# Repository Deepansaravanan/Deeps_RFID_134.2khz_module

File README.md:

Feedback Request
Hello! I have posted this project on GitHub but I'm unsure whether it is correct or if there are issues. If anyone with knowledge in this area can help me review or fix any problems, I would greatly appreciate your feedback and suggestions.

Please let me know if you spot mistakes, bugs, or unnecessary code.

Share advice on how I can improve the project or make it more robust.

If you have time, feel free to open an issue or pull request with corrections and explanations.

Thanks in advance for any help or feedback you can provide!

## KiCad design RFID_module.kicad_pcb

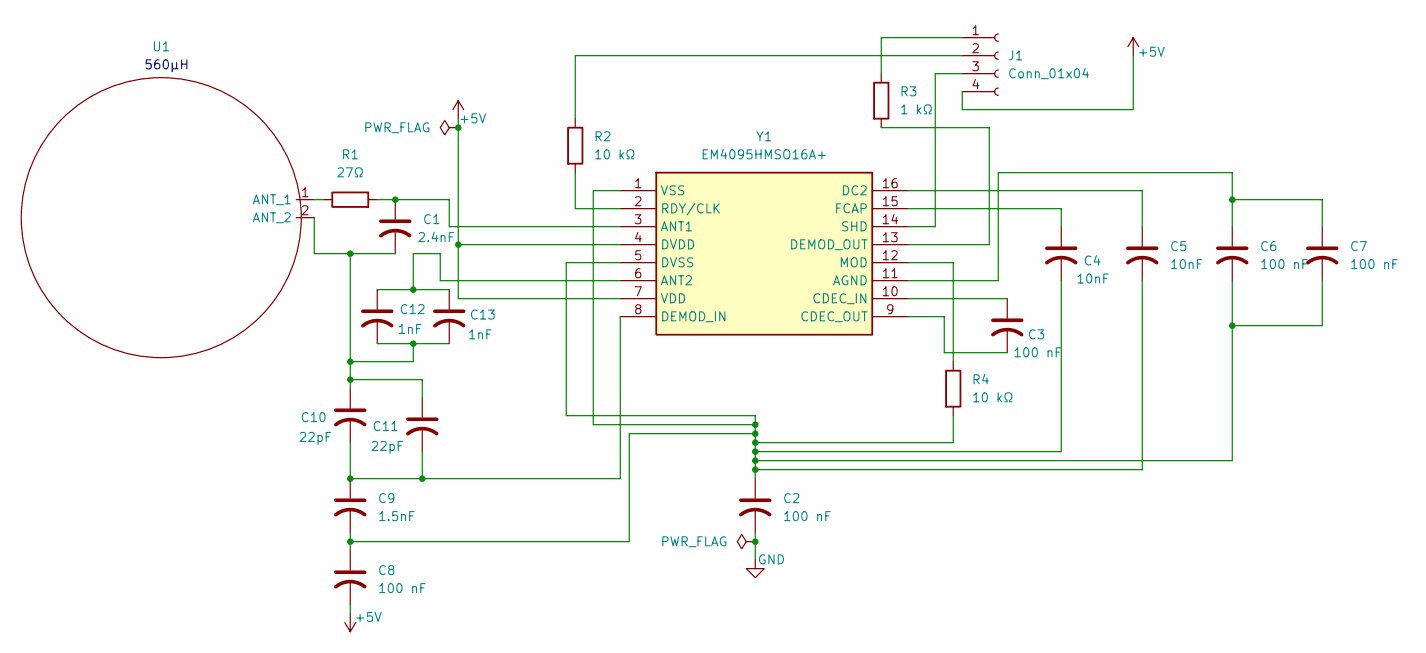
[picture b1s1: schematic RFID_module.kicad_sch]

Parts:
C1: 2.4nF; C_1808_4520Metric_Pad1.72x2.30mm_HandSolder
C2, C3, C6, C7, C8: 100 nF; C_1808_4520Metric_Pad1.72x2.30mm_HandSolder
C4, C5: 10nF; C_1808_4520Metric_Pad1.72x2.30mm_HandSolder
C9: 1.5nF; C_1808_4520Metric_Pad1.72x2.30mm_HandSolder
C10, C11: 22pF; C_1808_4520Metric_Pad1.72x2.30mm_HandSolder
C12, C13: 1nF; C_1808_4520Metric_Pad1.72x2.30mm_HandSolder
J1: Conn_01x04; PinHeader_1x04_P1.00mm_Vertical_SMD_Pin1Left
R1: 27Ω; R_0603_1608Metric_Pad0.98x0.95mm_HandSolder
R2, R4: 10 kΩ; R_0603_1608Metric_Pad0.98x0.95mm_HandSolder
R3: 1 kΩ; R_0603_1608Metric_Pad0.98x0.95mm_HandSolder
U1: 134.2khz_2
Y1: EM4095HMSO16A+; SO-16_3.9x9.9mm_P1.27mm; Manufacturer_Part_Number EM4095HMSO16A+

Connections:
+5V: C8.2, J1.4, Y1.4 (DVDD), Y1.7 (VDD)
GND: C2.2
unnamed: J1.1, R3.1
unnamed: J1.2, R2.1
unnamed: J1.3, Y1.14 (SHD)
unnamed: R1.1, U1.1 (ANT)
unnamed: C1.2, C10.1, C11.1, C12.2, C13.2, U1.2 (ANT)
unnamed: C6.1, C7.1, Y1.11 (AGND)
unnamed: C1.1, R1.2, Y1.3 (ANT1)
unnamed: C12.1, C13.1, Y1.6 (ANT2)
unnamed: C3.1, Y1.10 (CDEC_IN)
unnamed: C3.2, Y1.9 (CDEC_OUT)
unnamed: C5.1, Y1.16 (DC2)
unnamed: C9.1, C10.2, C11.2, Y1.8 (DEMOD_IN)
unnamed: R3.2, Y1.13 (DEMOD_OUT)
unnamed: C2.1, C4.2, C5.2, C6.2, C7.2, C8.1, C9.2, R4.2, Y1.1 (VSS), Y1.5 (DVSS)
unnamed: C4.1, Y1.15 (FCAP)
unnamed: R4.1, Y1.12 (MOD)
unnamed: R2.2, Y1.2 (RDY/CLK)

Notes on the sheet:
560μH

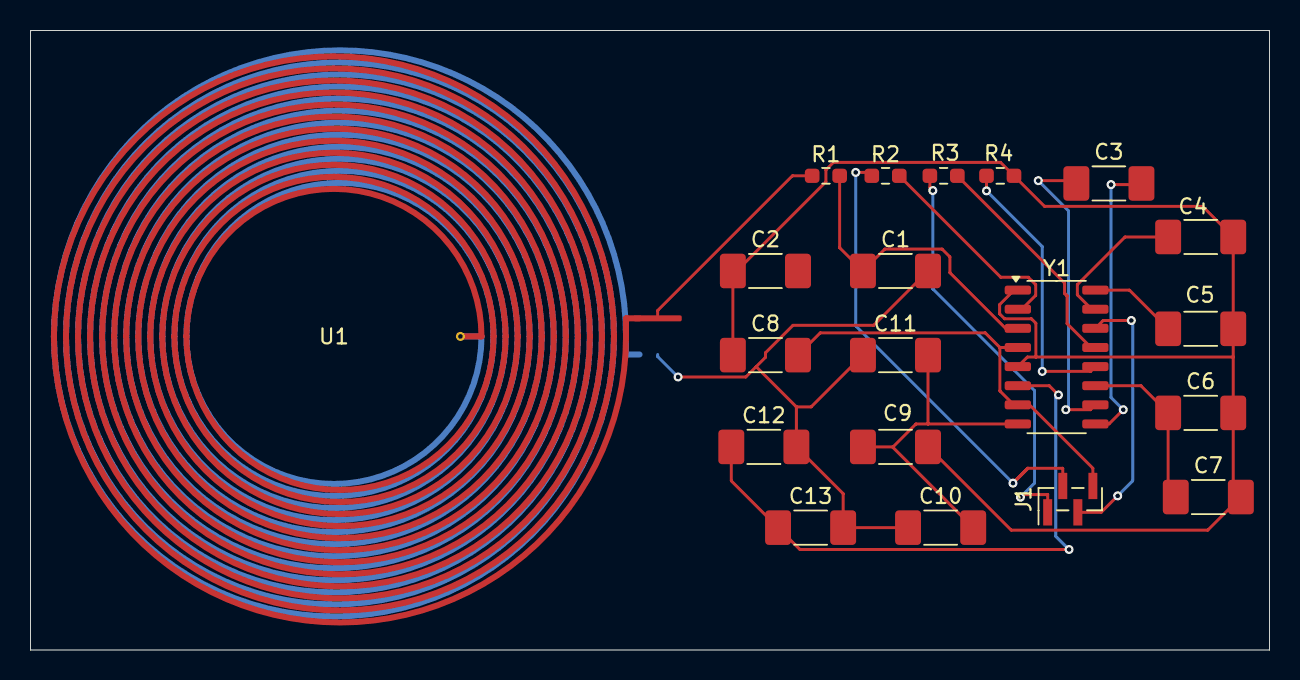
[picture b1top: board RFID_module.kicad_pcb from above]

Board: 2 copper layers, 82.3 x 41.1 mm, 20 parts (0 on the bottom side), 18 nets.
